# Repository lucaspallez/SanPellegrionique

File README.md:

# SanPellegrionique
Flight Avionics PCB for a Water Rocket  
This project was done in the scope of a project for the EPFL ENG-510 Space Propulsion Class

Embedded Software for this board available here: https://github.com/lucaspallez/COTS_SanPellegrinOS   
Compatible Ground Station PCB: https://github.com/lucaspallez/GRUND

## Features
- Computation: Arduino Nano v3
- Telemetry: RFM95W LoRa Module (with SMA connector)
- IMU: MPU 6050 Breakout
- Barometer: BMP 280 Breakout
- Power Output: 1 MOSFET Pyro output up to 3.6A
- Servo Output: 1 PWM output
- Power Inputs: 1x 2s LiPo Battery connector
- Arming: 1x Main external arm switch
- Status Indicators: 5x User programmable LEDs
- Battery voltage readings

## Documentation

Designed with KiCAD 6.0

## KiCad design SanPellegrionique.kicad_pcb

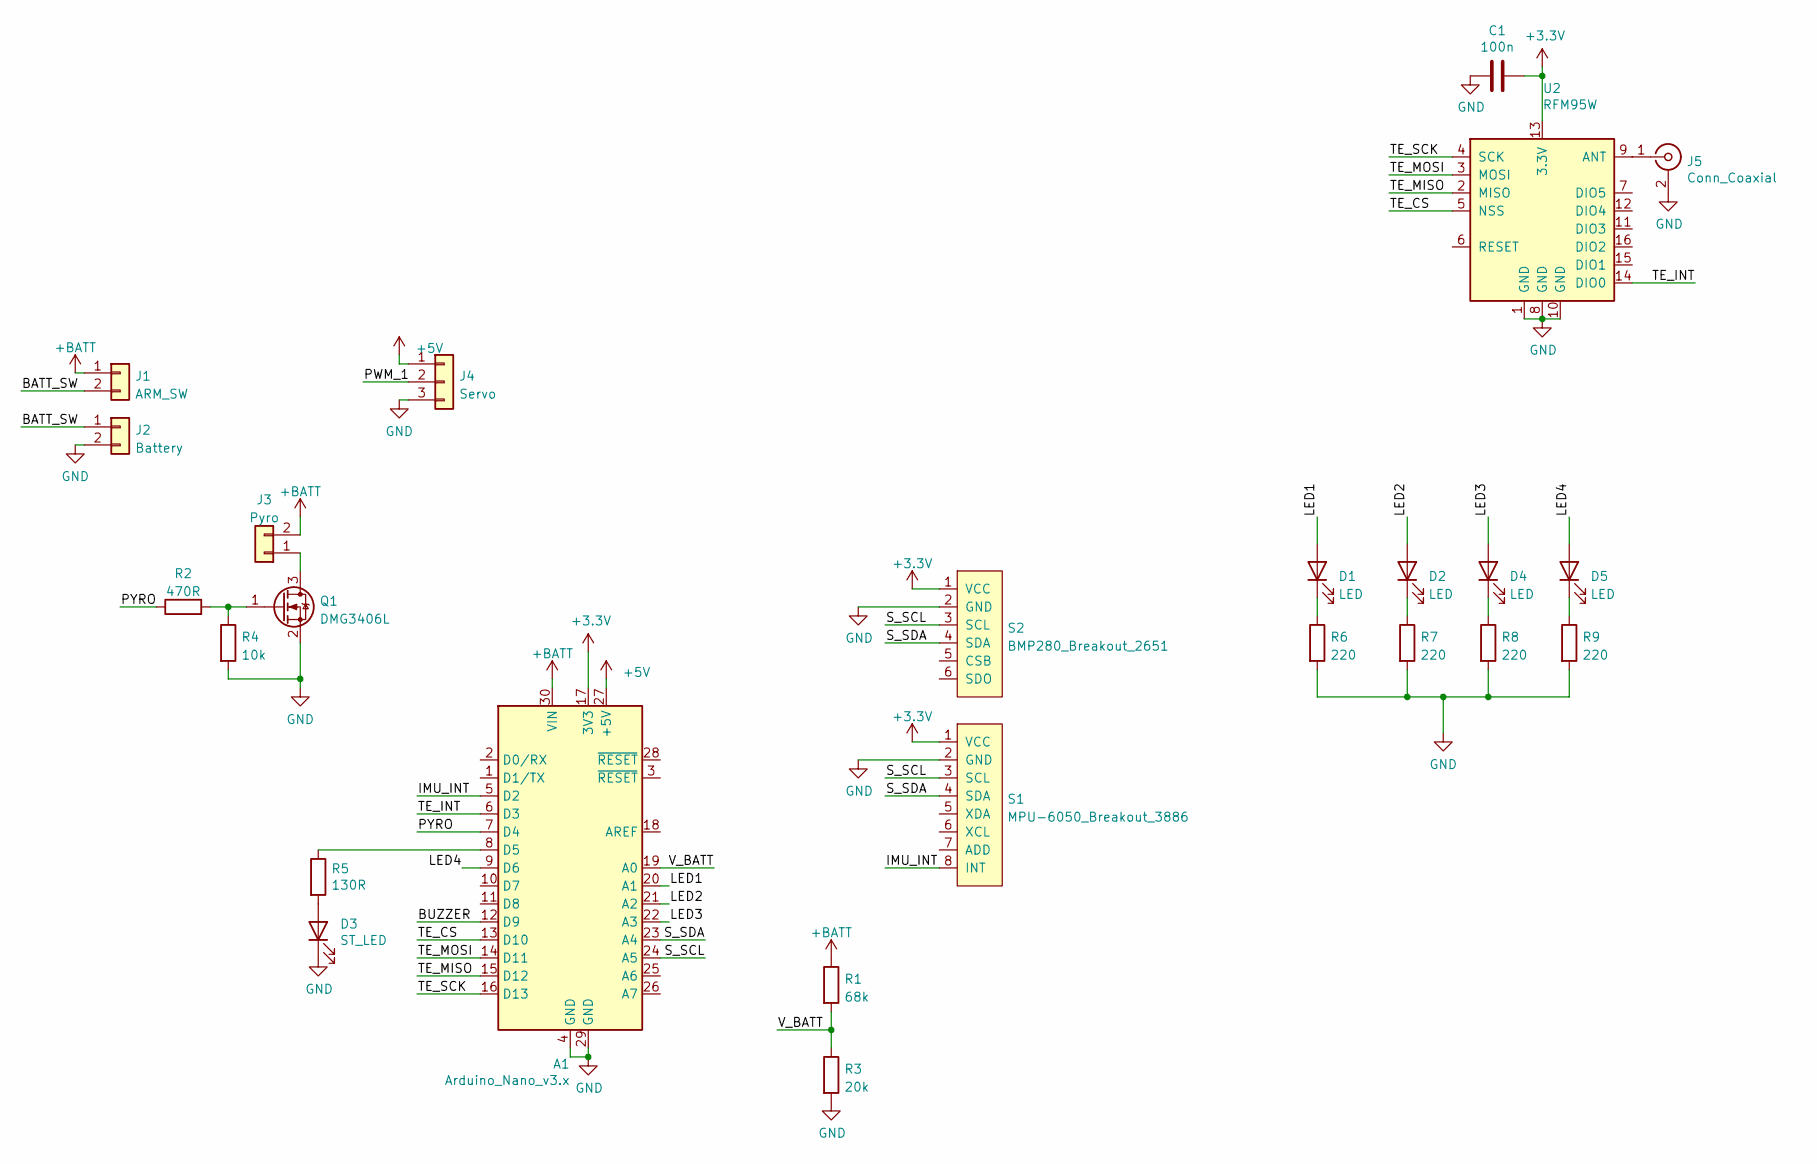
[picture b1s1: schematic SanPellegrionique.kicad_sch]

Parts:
A1: Arduino_Nano_v3.x; Arduino_Nano
C1: 100n; C_0805_2012Metric
D1, D2, D4, D5: LED; LED_0603_1608Metric_Pad1.05x0.95mm_HandSolder
D3: ST_LED; LED_0603_1608Metric
J1: ARM_SW; JST_PH_S2B-PH-K_1x02_P2.00mm_Horizontal
J2: Battery; JST_PH_S2B-PH-K_1x02_P2.00mm_Horizontal
J3: Pyro; JST_PH_S2B-PH-K_1x02_P2.00mm_Horizontal
J4: Servo; JST_PH_S3B-PH-K_1x03_P2.00mm_Horizontal
J5: Conn_Coaxial; SMA_Wurth_60312002114503_Vertical
Q1: DMG3406L; SOT-23
R1: 68k; R_0805_2012Metric_Pad1.20x1.40mm_HandSolder
R2: 470R; R_0805_2012Metric_Pad1.20x1.40mm_HandSolder
R3: 20k; R_0805_2012Metric_Pad1.20x1.40mm_HandSolder
R4: 10k; R_0805_2012Metric_Pad1.20x1.40mm_HandSolder
R5: 130R; R_0805_2012Metric_Pad1.20x1.40mm_HandSolder
R6, R7, R8, R9: 220; R_0805_2012Metric_Pad1.20x1.40mm_HandSolder
S1: MPU-6050_Breakout_3886; MPU_6050_Breakout
S2: BMP280_Breakout_2651; BMP_280_Breakout
U2: RFM95W; HOPERF_RFM9XW_SMD

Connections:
+3V3: A1.17 (3V3), C1.1, S1.1 (VCC), S2.1 (VCC), U2.13 (3.3V)
+5V: A1.27 (+5V), J4.1
+BATT: A1.30 (VIN), J1.1, J3.2, R1.1
/BATT_SW: J1.2, J2.1
/BUZZER: A1.12 (D9)
/IMU_INT: A1.5 (D2), S1.8 (INT)
/LED1: A1.20 (A1), D1.2 (A)
/LED2: A1.21 (A2), D2.2 (A)
/LED3: A1.22 (A3), D4.2 (A)
/LED4: A1.9 (D6), D5.2 (A)
/PWM_1: J4.2
/PYRO: A1.7 (D4), R2.1
/S_SCL: A1.24 (A5), S1.3 (SCL), S2.3 (SCL)
/S_SDA: A1.23 (A4), S1.4 (SDA), S2.4 (SDA)
/TE_CS: A1.13 (D10), U2.5 (NSS)
/TE_INT: A1.6 (D3), U2.14 (DIO0)
/TE_MISO: A1.15 (D12), U2.2 (MISO)
/TE_MOSI: A1.14 (D11), U2.3 (MOSI)
/TE_SCK: A1.16 (D13), U2.4 (SCK)
/V_BATT: A1.19 (A0), R1.2, R3.1
GND: A1.4 (GND), A1.29 (GND), C1.2, D3.1 (K), J2.2, J4.3, J5.2 (Ext), Q1.2 (S), R3.2, R4.2, R6.2, R7.2, R8.2, R9.2, S1.2 (GND), S2.2 (GND), U2.1 (GND), U2.8 (GND), U2.10 (GND)
unnamed: A1.8 (D5), R5.1
unnamed: D1.1 (K), R6.1
unnamed: D2.1 (K), R7.1
unnamed: D3.2 (A), R5.2
unnamed: D4.1 (K), R8.1
unnamed: D5.1 (K), R9.1
unnamed: J3.1, Q1.3 (D)
unnamed: J5.1 (In), U2.9 (ANT)
unnamed: Q1.1 (G), R2.2, R4.1

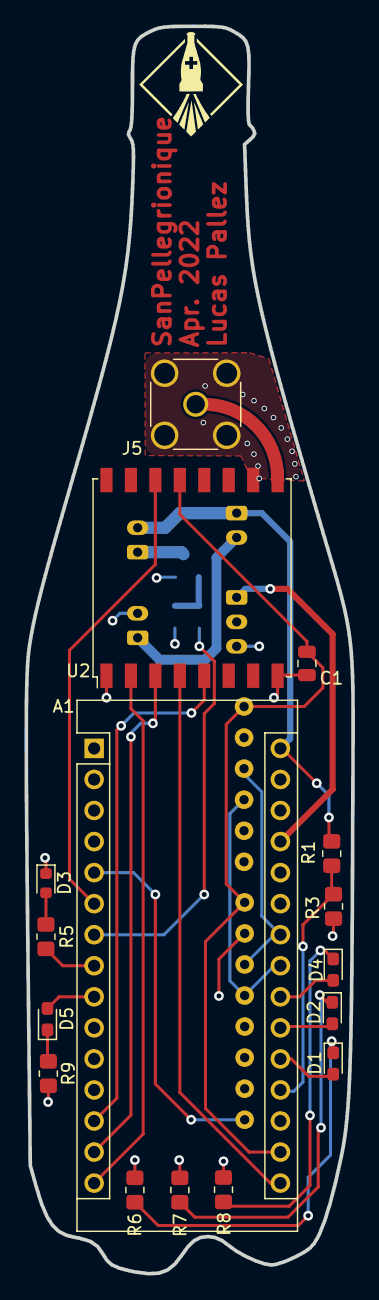
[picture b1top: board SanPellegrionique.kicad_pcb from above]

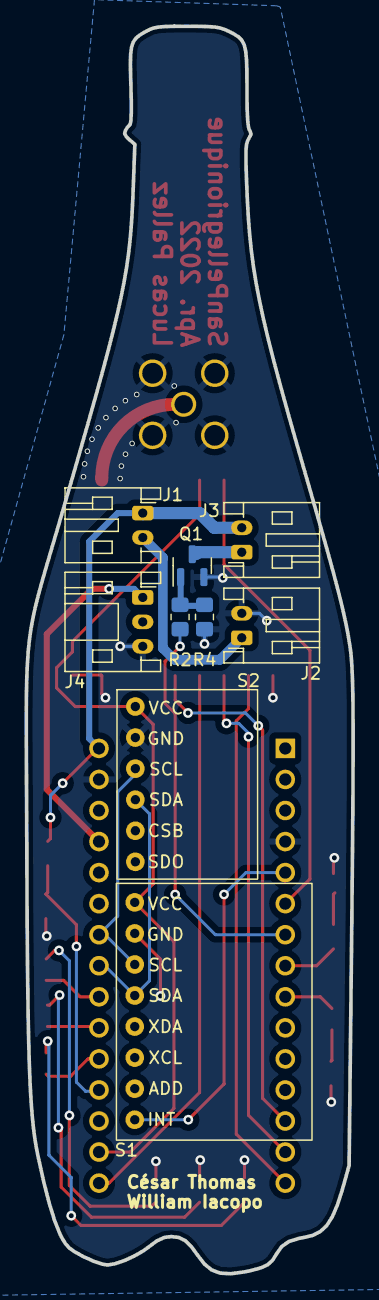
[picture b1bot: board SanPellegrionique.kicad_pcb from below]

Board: 2 copper layers, 26.7 x 102.0 mm, 25 parts (9 on the bottom side), 28 nets.

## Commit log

2022-05-21 Added gitignore
2022-05-21 SanPellegrionique R01 version
